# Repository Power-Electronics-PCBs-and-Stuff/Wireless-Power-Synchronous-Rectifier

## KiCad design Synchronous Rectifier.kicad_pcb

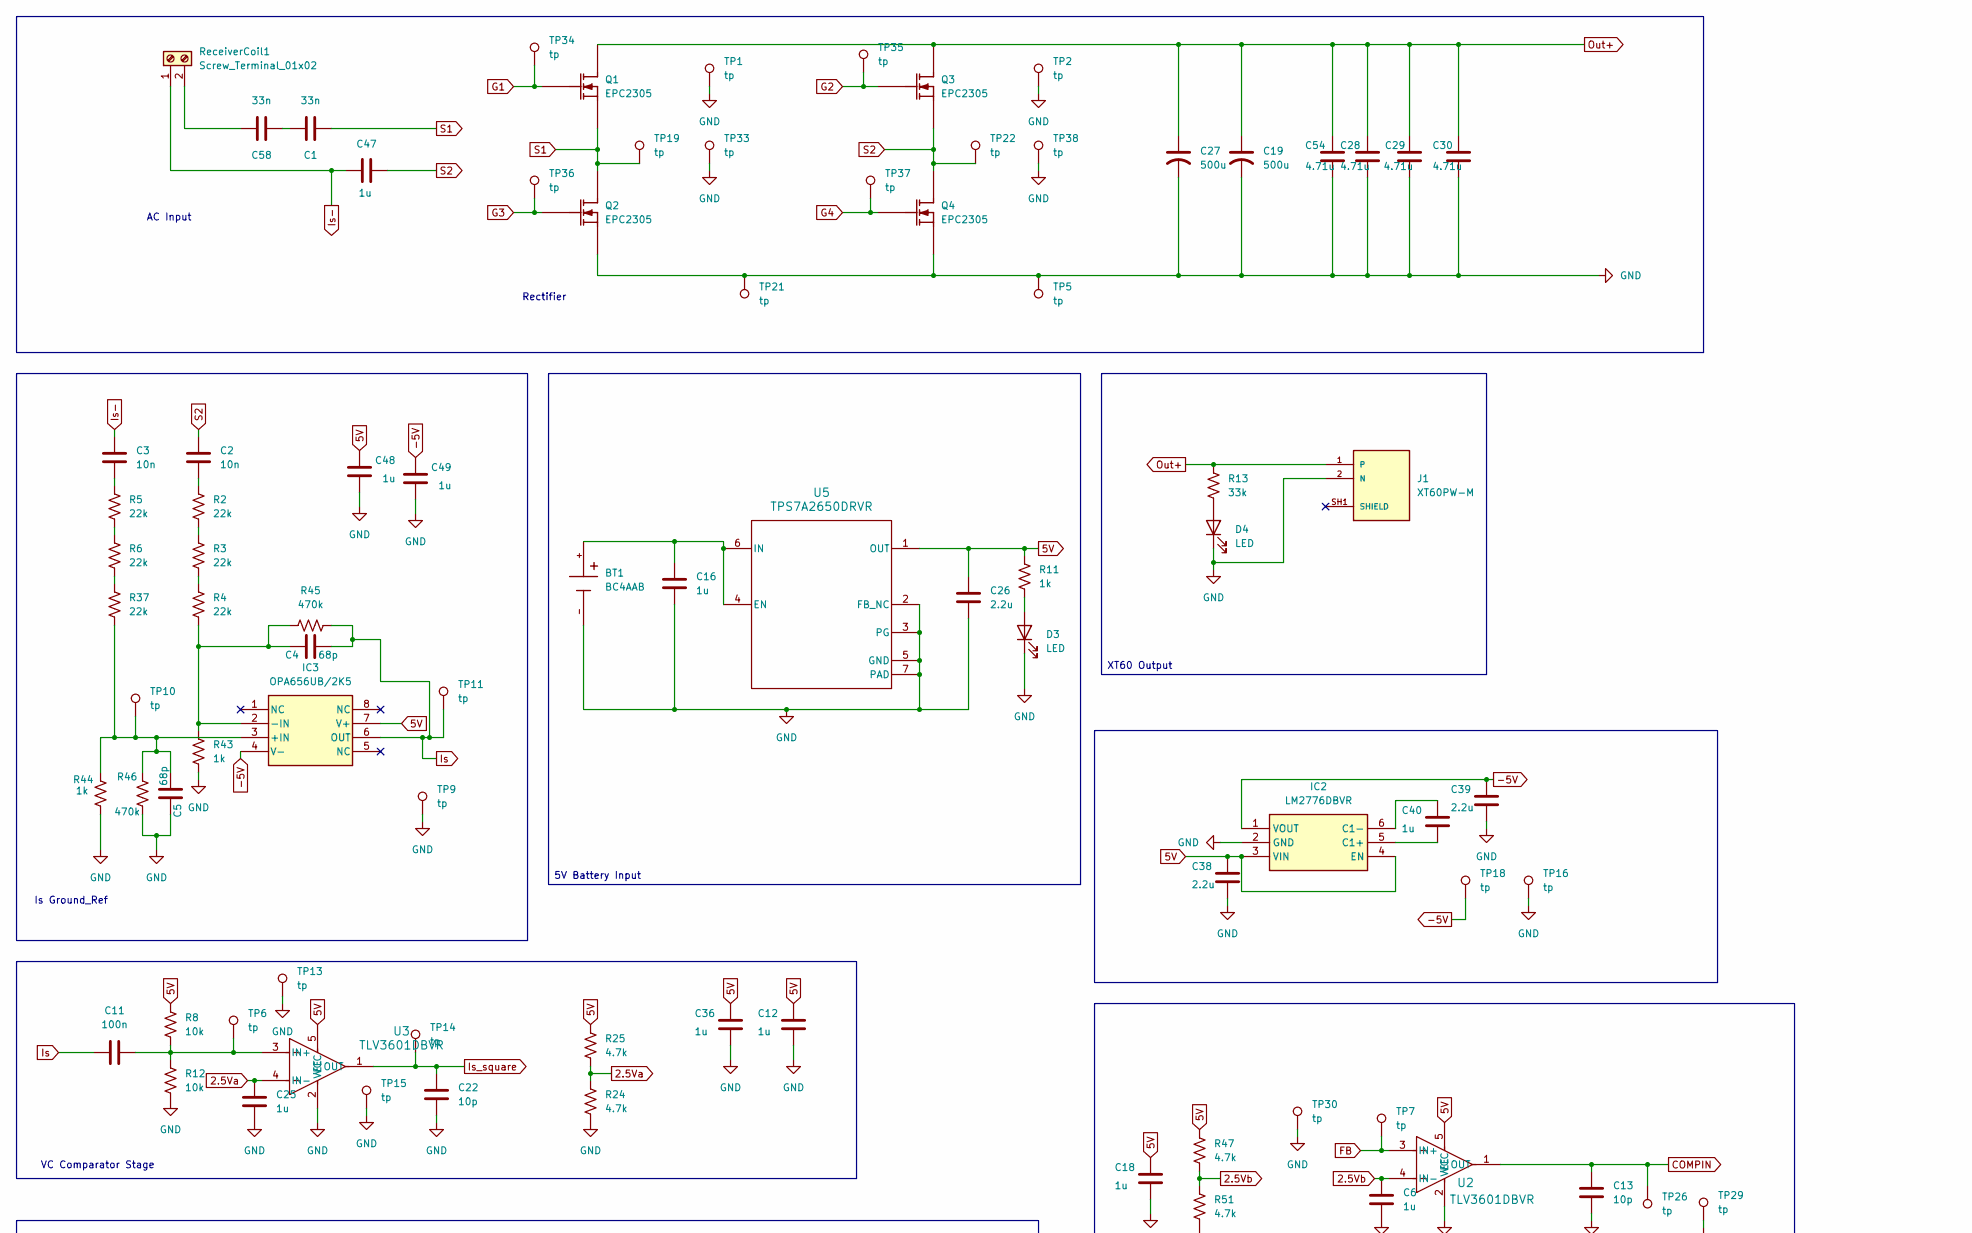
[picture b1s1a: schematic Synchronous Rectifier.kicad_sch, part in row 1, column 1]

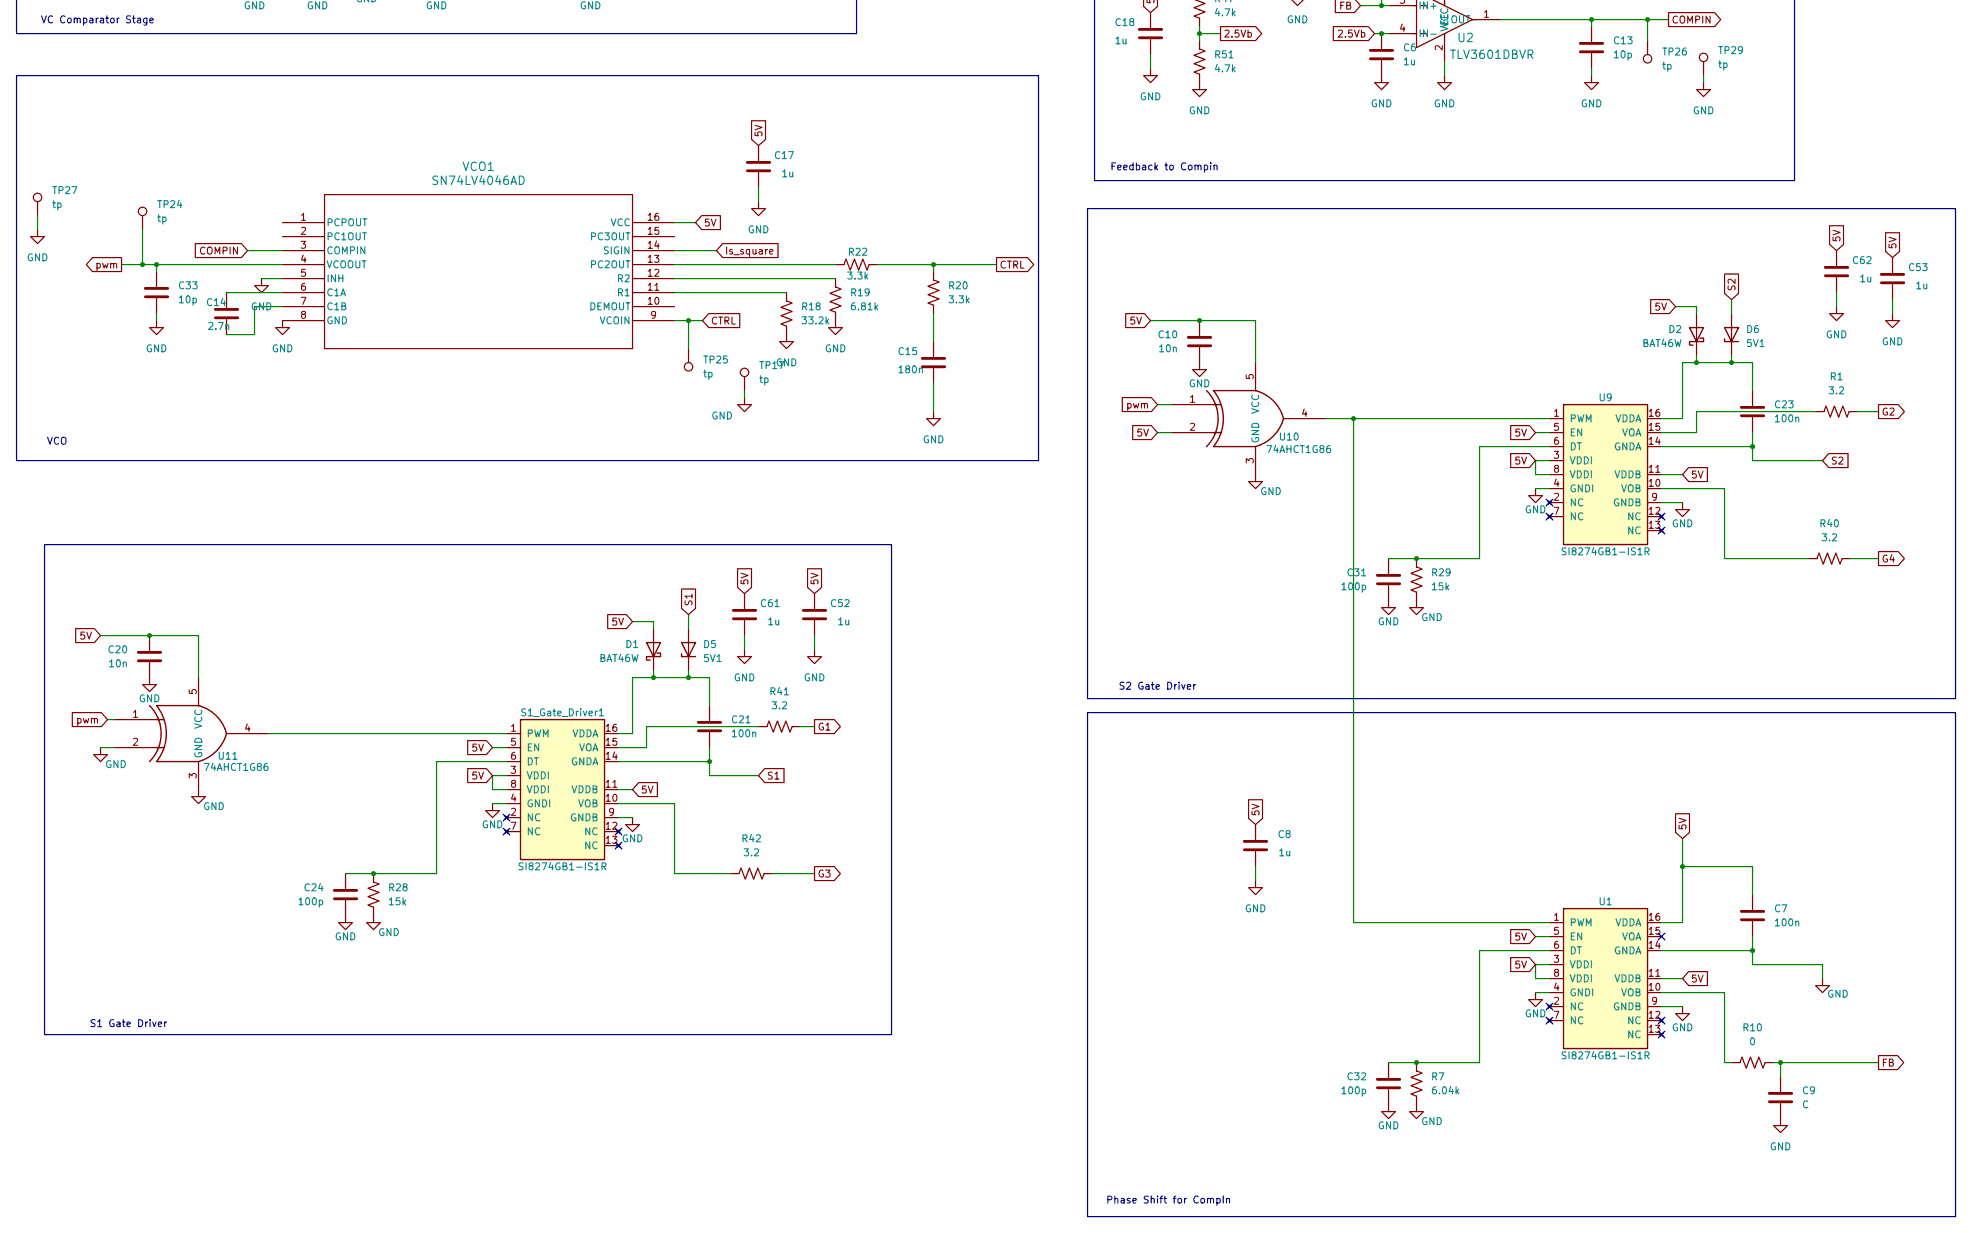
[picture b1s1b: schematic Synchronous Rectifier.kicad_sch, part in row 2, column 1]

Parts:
BT1: BC4AAB; BAT_BC4AAB; PARTREV E; DigiKey_Part_Number BC4AAB-ND
C1, C58: 33n; C_1206_3216Metric
C2, C3, C10, C20: 10n; C_0603_1608Metric
C4, C5: 68p; C_0603_1608Metric
C6, C8, C12, C16, C17, C18, C25, C36, C40, C48, C49, C52, C53, C61, C62: 1u; C_0603_1608Metric
C7, C11, C21, C23: 100n; C_0603_1608Metric
C9: C; C_0603_1608Metric
C13, C22, C33: 10p; C_0603_1608Metric
C14: 2.7n; C_0603_1608Metric
C15: 180n; C_0603_1608Metric
C19, C27: 500u; CP_Radial_D16.0mm_P7.50mm
C24, C31, C32: 100p; C_0603_1608Metric
C26, C38, C39: 2.2u; C_0603_1608Metric
C28, C29, C30, C54: 4.71u; C_1206_3216Metric
C47: 1u; C_1206_3216Metric
D1, D2: BAT46W; D_SOD-123F
D3, D4: LED; LED_0603_1608Metric
D5, D6: 5V1; D_SOD-123; MPN MMSZ5231B
IC2: LM2776DBVR; DBV0006A_N; Mouser Part Number 595-LM2776DBVR
IC3: OPA656UB/2K5; D8; Mouser Part Number 584-ADA4817-1ARDZ-R7
J1: XT60PW-M; AMASS_XT60PW-M; PARTREV 1.2
Q1, Q2, Q3, Q4: EPC2305; Manufacturer_Part_Number EPC2305
R1, R40, R41, R42: 3.2; R_0603_1608Metric
R2, R3, R4, R5, R6, R37: 22k; R_0603_1608Metric
R7: 6.04k; R_0603_1608Metric
R8, R12: 10k; R_0603_1608Metric
R10: 0; R_0603_1608Metric
R11, R43, R44: 1k; R_0603_1608Metric
R13: 33k; R_0603_1608Metric
R18: 33.2k; R_0603_1608Metric
R19: 6.81k; R_0603_1608Metric
R20, R22: 3.3k; R_0603_1608Metric
R24, R25, R47, R51: 4.7k; R_0603_1608Metric
R28, R29: 15k; R_0603_1608Metric
R45, R46: 470k; R_0603_1608Metric
ReceiverCoil1: Screw_Terminal_01x02; Molex_0389690002
S1_Gate_Driver1: SI8274GB1-IS1R; SOIC-16_3.9x9.9mm_P1.27mm; MPN SI8274GB1-IS1R
TP1, TP2, TP5, TP6, TP7, TP9, TP10, TP11, TP13, TP14, TP15, TP16, TP17, TP18, TP19, TP21, TP22, TP24, TP25, TP26, TP27, TP29, TP30, TP33, TP34, TP35, TP36, TP37, TP38: tp; TestPoint_THTPad_D2.0mm_Drill1.0mm
U1, U9: SI8274GB1-IS1R; SOIC-16_3.9x9.9mm_P1.27mm; MPN SI8274GB1-IS1R
U2: TLV3601DBVR; TSOT-23-5_HandSoldering
U3: TLV3601DBVR; SOT-23-5_HandSoldering
U5: TPS7A2650DRVR; DRV0006A_NV
U10, U11: 74AHCT1G86; DBV5
VCO1: SN74LV4046AD; D16

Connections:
2.5Va: C25.2, R24.1, R25.2, U3.4 (IN-)
2.5Vb: C6.2, R47.2, R51.1, U2.4 (IN-)
5V: C7.1, C8.2, C10.1, C12.2, C17.2, C18.2, C20.1, C26.1, C36.2, C38.2, C48.2, C52.2, C53.2, C61.2, C62.2, D1.2 (A), D2.2 (A), IC2.3 (VIN), IC2.4 (EN), IC3.7 (V+), R8.1, R11.1, R25.1, R47.1, S1_Gate_Driver1.3 (VDDI), S1_Gate_Driver1.5 (EN), S1_Gate_Driver1.8 (VDDI), S1_Gate_Driver1.11 (VDDB), U1.3 (VDDI), U1.5 (EN), U1.8 (VDDI), U1.11 (VDDB), U1.16 (VDDA), U2.5 (VCC), U3.5 (VCC), U5.1 (OUT), U9.3 (VDDI), U9.5 (EN), U9.8 (VDDI), U9.11 (VDDB), U10.2, U10.5 (VCC), U11.5 (VCC), VCO1.16 (VCC)
-5V: C39.2, C49.2, IC2.1 (VOUT), IC3.4 (V-), TP18.1 (1_1)
COMPIN: C13.1, TP26.1 (1_1), U2.1 (OUT), VCO1.3 (COMPIN)
CTRL: R20.1, R22.1, TP25.1 (1_1), VCO1.9 (VCOIN)
FB: C9.1, R10.2, TP7.1 (1_1), U2.3 (IN+)
G1: Q1.1 (G_1), Q1.12 (G_2), R41.2, TP34.1 (1_1)
G2: Q3.1 (G_1), Q3.12 (G_2), R1.2, TP35.1 (1_1)
G3: Q2.1 (G_1), Q2.12 (G_2), R42.2, TP36.1 (1_1)
G4: Q4.1 (G_1), Q4.12 (G_2), R40.2, TP37.1 (1_1)
GND: BT1.-, C5.2, C6.1, C7.2, C8.1, C9.2, C10.2, C12.1, C13.2, C15.1, C16.2, C17.1, C18.1, C19.2, C20.2, C22.2, C24.2, C25.1, C26.2, C27.2, C28.1, C29.1, C30.1, C31.2, C32.2, C33.2, C36.1, C38.1, C39.1, C48.1, C49.1, C52.1, C53.1, C54.1, C61.1, C62.1, D3.1 (K), D4.1 (K), IC2.2 (GND), J1.2 (N), Q2.2 (S_1), Q2.4 (S_2), Q2.6 (S_3), Q2.13 (S_4), Q2.14 (S_5), Q2.15 (S_6), Q4.2 (S_1), Q4.4 (S_2), Q4.6 (S_3), Q4.13 (S_4), Q4.14 (S_5), Q4.15 (S_6), R7.2, R12.1, R18.1, R19.1, R24.2, R28.2, R29.2, R43.2, R44.2, R46.1, R51.2, S1_Gate_Driver1.4 (GNDI), S1_Gate_Driver1.9 (GNDB), TP1.1 (1_1), TP2.1 (1_1), TP5.1 (1_1), TP9.1 (1_1), TP13.1 (1_1), TP15.1 (1_1), TP16.1 (1_1), TP17.1 (1_1), TP21.1 (1_1), TP27.1 (1_1), TP29.1 (1_1), TP30.1 (1_1), TP33.1 (1_1), TP38.1 (1_1), U1.4 (GNDI), U1.9 (GNDB), U1.14 (GNDA), U2.2 (VEE), U3.2 (VEE), U5.2 (FB_NC), U5.3 (PG), U5.5 (GND), U5.7 (PAD), U9.4 (GNDI), U9.9 (GNDB), U10.3 (GND), U11.2, U11.3 (GND), VCO1.5 (INH), VCO1.8 (GND)
Is: C4.1, C11.1, IC3.6 (OUT), R45.2, TP11.1 (1_1)
Is-: C3.1, C47.2, ReceiverCoil1.1
Is_square: C22.1, TP14.1 (1_1), U3.1 (OUT), VCO1.14 (SIGIN)
unnamed: C1.1, C58.2
unnamed: C2.2, R2.1
unnamed: C3.2, R5.1
unnamed: C15.2, R20.2
unnamed: C21.1, D1.1 (K), D5.1 (K), S1_Gate_Driver1.16 (VDDA)
unnamed: C23.1, D2.1 (K), D6.1 (K), U9.16 (VDDA)
unnamed: D3.2 (A), R11.2
unnamed: D4.2 (A), R13.2
unnamed: C40.1, IC2.5 (C1+)
unnamed: C40.2, IC2.6 (C1-)
unnamed: C5.1, IC3.3 (+IN), R37.2, R44.1, R46.2, TP10.1 (1_1)
unnamed: C4.2, IC3.2 (-IN), R4.2, R43.1, R45.1
unnamed: R2.2, R3.1
unnamed: R3.2, R4.1
unnamed: R5.2, R6.1
unnamed: R6.2, R37.1
unnamed: C58.1, ReceiverCoil1.2
unnamed: C24.1, R28.1, S1_Gate_Driver1.6 (DT)
unnamed: S1_Gate_Driver1.1 (PWM), U11.4
unnamed: R41.1, S1_Gate_Driver1.15 (VOA)
unnamed: R42.1, S1_Gate_Driver1.10 (VOB)
unnamed: C32.1, R7.1, U1.6 (DT)
unnamed: U1.1 (PWM), U9.1 (PWM), U10.4
unnamed: R10.1, U1.10 (VOB)
unnamed: C11.2, R8.2, R12.2, TP6.1 (1_1), U3.3 (IN+)
unnamed: BT1.+, C16.1, U5.4 (EN), U5.6 (IN)
unnamed: C31.1, R29.1, U9.6 (DT)
unnamed: R1.1, U9.15 (VOA)
unnamed: R40.1, U9.10 (VOB)
unnamed: C14.2, VCO1.6 (C1A)
unnamed: C14.1, VCO1.7 (C1B)
unnamed: R22.2, VCO1.13 (PC2OUT)
unnamed: R18.2, VCO1.11 (R1)
unnamed: R19.2, VCO1.12 (R2)
Out+: C19.1, C27.1, C28.2, C29.2, C30.2, C54.2, J1.1, Q1.3 (D_1), Q1.5 (D_2), Q1.7 (D_3), Q1.8 (D_4), Q1.9 (D_5), Q1.10 (D_6), Q1.11 (D_7), Q3.3 (D_1), Q3.5 (D_2), Q3.7 (D_3), Q3.8 (D_4), Q3.9 (D_5), Q3.10 (D_6), Q3.11 (D_7), R13.1
S1: C1.2, C21.2, D5.2 (A), Q1.2 (S_1), Q1.4 (S_2), Q1.6 (S_3), Q1.13 (S_4), Q1.14 (S_5), Q1.15 (S_6), Q2.3 (D_1), Q2.5 (D_2), Q2.7 (D_3), Q2.8 (D_4), Q2.9 (D_5), Q2.10 (D_6), Q2.11 (D_7), S1_Gate_Driver1.14 (GNDA), TP19.1 (1_1)
S2: C2.1, C23.2, C47.1, D6.2 (A), Q3.2 (S_1), Q3.4 (S_2), Q3.6 (S_3), Q3.13 (S_4), Q3.14 (S_5), Q3.15 (S_6), Q4.3 (D_1), Q4.5 (D_2), Q4.7 (D_3), Q4.8 (D_4), Q4.9 (D_5), Q4.10 (D_6), Q4.11 (D_7), TP22.1 (1_1), U9.14 (GNDA)
pwm: C33.1, TP24.1 (1_1), U10.1, U11.1, VCO1.4 (VCOOUT)

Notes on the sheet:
VCO
S2 Gate Driver
Feedback to Compin
VC Comparator Stage
S1 Gate Driver
Rectifier
Is Ground_Ref
AC Input
Phase Shift for CompIn
XT60 Output
5V Battery Input

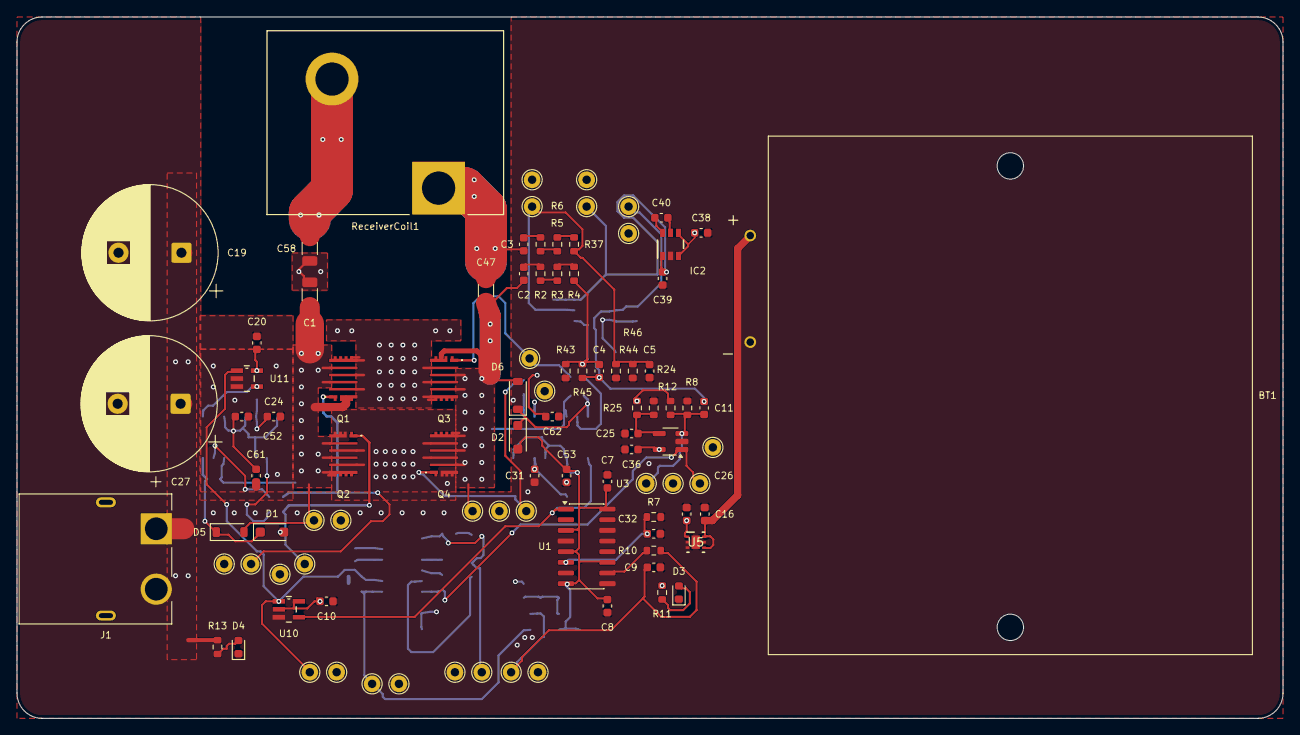
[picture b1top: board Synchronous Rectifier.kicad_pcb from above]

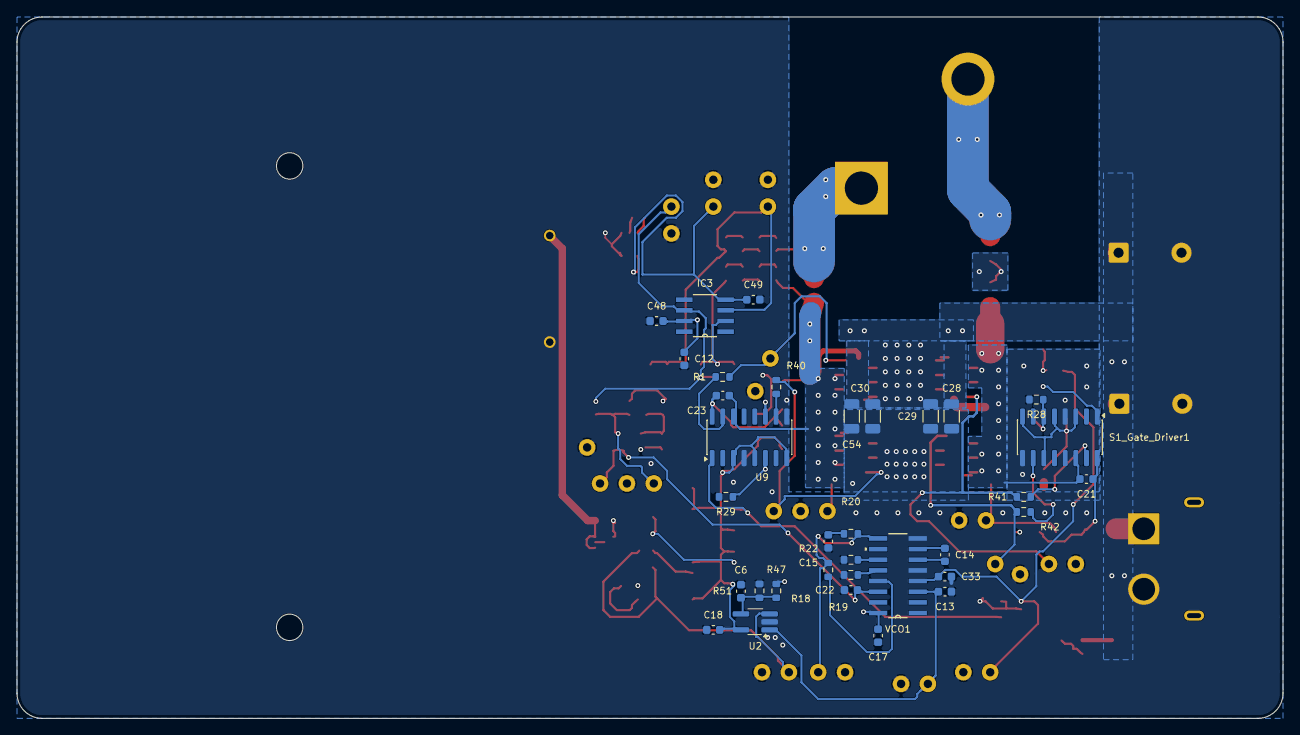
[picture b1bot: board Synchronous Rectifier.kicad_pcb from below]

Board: 4 copper layers, 150.9 x 83.6 mm, 129 parts (34 on the bottom side), 53 nets.

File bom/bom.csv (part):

Reference,Qty,Value,Footprint,MPN,Manufacturer,DigiKey,DK_Stock,Mouser,MO_Stock,Chosen_Distributor,Datasheet,Validated,DNP,Notes
BT1,1,BC4AAB,BAT_BC4AAB,BC4AAB,MPD,BC4AAB-ND,16,,,DigiKey,,yes (digikey.com page 2026-11-09),,"DigiKey shows 16 on hand + 13,400 factory stock"
"C1,C58",2,33n,1206,,,,,,,,,no,,UNSOURCED: 33 nF in series with the coil sees ~11 A RMS and ~210 V RMS at 250 kHz; no single 1206 part exists. Needs a parallel C0G bank (e.g. 10x KEMET C1206C332JCGACAUTO 3.3 nF 500 V C0G) or a film capacitor; schematic/PCB change required
"C3,C10,C20,C2",4,10n,0603,CL10B103KB8NNNC,Samsung Electro-Mechanics,1276-1009-1-ND,5504,,,DigiKey,,yes (digikey.com page 2026-11-09),,10 nF 50 V X7R 0603
"C4,C5",2,68p,0603,CL10C680JB8NNNC,Samsung Electro-Mechanics,1276-1135-1-ND,207000,,,DigiKey,,yes (digikey.com page 2026-11-09),,68 pF 50 V C0G 0603
C9,1,C,0603,,,,,,,,,no,,"UNSOURCED: schematic value is ""C"" (no capacitance given) - set the value first"
"C11,C23,C7,C21",4,100n,0603,C0603C104K5RACTU,KEMET,399-C0603C104K5RACTUCT-ND,2485421,,,DigiKey,,yes (digikey.com page 2026-11-09),,100 nF 50 V X7R 0603 (Samsung CL10B104KB8NNNC is on 61-week backorder)
"C13,C33,C22",3,10p,0603,CL10C100JB8NNNC,Samsung Electro-Mechanics,1276-1027-1-ND,206747,,,DigiKey,,yes (digikey.com page 2026-11-09),,10 pF 50 V C0G 0603
C14,1,2.7n,0603,GRM1885C1H272JA01D,Murata Electronics,490-3283-1-ND,293979,,,DigiKey,,yes (digikey.com page 2026-11-09),,2.7 nF 50 V C0G 0603
C15,1,180n,0603,CC0603KRX7R8BB184,YAGEO,13-CC0603KRX7R8BB184CT-ND,19322,,,DigiKey,,yes (digikey.com page 2026-11-09),,180 nF 25 V X7R 0603 (no 50 V 0.18 uF 0603 stocked; node is 5 V)
"C19,C27",2,500u,CP_Radial_D16.0mm_P7.50mm,UPW2A471MHD,Nichicon,493-1985-ND,5222,,,DigiKey,,yes (digikey.com page 2026-11-09),,"470 uF 100 V substituted for 500 uF; 16 mm dia, 7.5 mm pitch, 31.5 mm tall; ripple 1.31 A @100 kHz; status Not-For-New-Designs (Panasonic EEU-FC2A471 is obsolete)"
"C32,C24,C31",3,100p,0603,CL10C101JB8NNNC,Samsung Electro-Mechanics,1276-1008-1-ND,1155305,,,DigiKey,,yes (digikey.com page 2026-11-09),,100 pF 50 V C0G 0603
"C38,C26,C39",3,2.2u,0603,GRM188Z71E225KE43D,Murata Electronics,490-GRM188Z71E225KE43DCT-ND,147724,,,DigiKey,,yes (digikey.com page 2026-11-09),,"2.2 uF 25 V 0603 (DigiKey lists X7R; Murata ""Z7"" code is X7T class)"
"C40,C16,C36,C6,C17,C8,C49,C52,C18,C53,C62,C61,C25,C48,C12",15,1u,0603,UMK107AB7105KA-T,Taiyo Yuden,587-3247-1-ND,579237,,,DigiKey,,yes (digikey.com page 2026-11-09),,1 uF 50 V X7R 0603
C47,1,1u,1206,C1206C105K1RACTU,KEMET,399-C1206C105K1RACTUCT-ND,31698,,,DigiKey,,yes (digikey.com page 2026-11-09),,1 uF 100 V X7R 1206 (Murata GRM31CR72A105KA01L backordered to Feb 2027). Also in the 11 A tank path - same cap-bank concern as C1/C58
"C54,C28,C30,C29",4,4.71u,1206,GRJ31CZ72A475KE01L,Murata Electronics,490-GRJ31CZ72A475KE01LCT-ND,66536,,,DigiKey,,yes (digikey.com page 2026-11-09),,4.7 uF 100 V X7R 1206 soft-termination (GRM31CR72A475KE11L not stocked)
"D2,D1",2,BAT46W,SOD-123F,BAT46W,Diotec Semiconductor,4878-BAT46WCT-ND,83359,,,DigiKey,https://datasheet.lcsc.com/lcsc/2204281430_Guangdong-Hottech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,yes (digikey.com page 2026-11-09),,SOD-123 part on the SOD-123F footprint (pad pitch compatible). Vishay BAT46W-E3-08 backordered to Jan 2027
"D3,D4",2,LED,0603,LTST-C190GKT,Lite-On Inc.,160-LTST-C190GKTCT-ND,1187734,,,DigiKey,,yes (digikey.com page 2026-11-09),,green 0603 LED
"D6,D5",2,5V1,SOD-123,MMSZ5231BT1G,onsemi,MMSZ5231BT1GOSCT-ND,76458,,,DigiKey,https://www.onsemi.com/pdf/datasheet/mmsz5221bt1-d.pdf,yes (digikey.com page 2026-11-09),,5.1 V 500 mW Zener SOD-123
IC2,1,LM2776DBVR,DBV0006A_N,LM2776DBVR,Texas Instruments,296-43957-1-ND,46809,595-LM2776DBVR,,DigiKey,http://www.ti.com/lit/gpn/lm2776,yes (digikey.com page 2026-11-09),,
IC3,1,OPA656UB/2K5,D8,OPA656UB/2K5,Texas Instruments,296-OPA656UB/2K5CT-ND,3184,584-ADA4817-1ARDZ-R7,,DigiKey,https://www.ti.com/lit/gpn/opa656,yes (digikey.com page 2026-11-09),,schematic MPN field said ADA4817-1ARDZ-R7 (left over from the sample board) - corrected to the OPA656 the symbol and footprint describe
J1,1,XT60PW-M,AMASS_XT60PW-M,XT60PW-M,AMASS,,,,,Amazon,,no,,"AMAZON: right-angle PCB-mount XT60 male; candidate listings B0DTGCK8VF (Gaslos, 90-degree XT60PW male/female) and B07VRLQ2C5 (Yiqigou, XT60PW pairs). Amazon blocks automated browsing - confirm the listing shows the XT60PW-M (male, PCB, 90 degree) before ordering"
"Q4,Q1,Q2,Q3",4,EPC2305,EPC2305,EPC2305,EPC,917-EPC2305CT-ND,15878,,,DigiKey,https://epc-co.com/epc/products/gan-fets-and-ics/epc2305,yes (digikey.com page 2026-11-09),,150 V GaN FET
"R1,R40,R41,R42",4,3.2,0603,ERJ-3RQF3R3V,Panasonic Industry,P3.3AJCT-ND,5604,,,DigiKey,,yes (digikey.com page 2026-11-09),,3.3 ohm substituted for 3.2 ohm (3.2 is not an E24/E96 value stocked in 0603)
R7,1,6.04k,0603,ERJ-3EKF6041V,Panasonic Industry,P6.04KHCT-ND,36474,,,DigiKey,,yes (digikey.com page 2026-11-09),,
"R8,R12",2,10k,0603,ERJ-3EKF1002V,Panasonic Industry,P10.0KHCT-ND,621467,,,DigiKey,,yes (digikey.com page 2026-11-09),,
R10,1,0,0603,ERJ-3GEY0R00V,Panasonic Industry,P0.0GCT-ND,4415369,,,DigiKey,,yes (digikey.com page 2026-11-09),,0 ohm jumper
"R11,R43,R44",3,1k,0603,ERJ-3EKF1001V,Panasonic Industry,P1.00KHCT-ND,4055833,,,DigiKey,,yes (digikey.com page 2026-11-09),,
R13,1,33k,0603,ERJ-3EKF3302V,Panasonic Industry,P33.0KHCT-ND,93742,,,DigiKey,,yes (digikey.com page 2026-11-09),,
R18,1,33.2k,0603,ERJ-3EKF3322V,Panasonic Industry,P33.2KHCT-ND,89962,,,DigiKey,,yes (digikey.com page 2026-11-09),,
R19,1,6.81k,0603,ERJ-3EKF6811V,Panasonic Industry,P6.81KHCT-ND,1074,,,DigiKey,,yes (digikey.com page 2026-11-09),,DigiKey page is tagged Marketplace - may ship separately
"R20,R22",2,3.3k,0603,ERJ-3EKF3301V,Panasonic Industry,P3.30KHCT-ND,359068,,,DigiKey,,yes (digikey.com page 2026-11-09),,
"R24,R51,R25,R47",4,4.7k,0603,ERJ-3EKF4701V,Panasonic Industry,P4.70KHCT-ND,783994,,,DigiKey,,yes (digikey.com page 2026-11-09),,
"R29,R28",2,15k,0603,ERJ-3EKF1502V,Panasonic Industry,P15.0KHCT-ND,48445,,,DigiKey,,yes (digikey.com page 2026-11-09),,
"R37,R4,R2,R6,R5,R3",6,22k,0603,ERJ-3EKF2202V,Panasonic Industry,P22.0KHCT-ND,184599,,,DigiKey,,yes (digikey.com page 2026-11-09),,
"R45,R46",2,470k,0603,ERJ-3EKF4703V,Panasonic Industry,P470KHCT-ND,50008,,,DigiKey,,yes (digikey.com page 2026-11-09),,
ReceiverCoil1,1,Screw_Terminal_01x02,Molex_0389690002,0389690002,Molex,WM7469-ND,4511,,,DigiKey,,yes (digikey.com page 2026-11-09),,"2-circuit barrier terminal block, 12.7 mm pitch, PC-pin"
"S1_Gate_Driver1,U9,U1",3,SI8274GB1-IS1R,SOIC-16_3.9x9.9mm_P1.27mm,SI8274GB1-IS1R,Skyworks Solutions Inc.,336-5554-1-ND,1683,,,DigiKey,https://www.skyworksinc.com/Products/Isolation/Si827x-Isolat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,yes (digikey.com page 2026-11-09),,
"TP27,TP16,TP22,TP25,TP33,TP24,TP15,TP11,TP36,TP10,TP14,TP29,TP1,TP26,TP7,TP21,TP13,TP19,TP5,TP17,TP35,TP2,TP6,TP37,TP18,TP9,TP38,TP30,TP34",29,tp,TestPoint_THTPad_D2.0mm_Drill1.0mm,,,,,,,,,n/a,,bare 2 mm PTH test pad - nothing to order
U2,1,TLV3601DBVR,TSOT-23-5_HandSoldering,TLV3601DBVR,Texas Instruments,296-TLV3601DBVRCT-ND,5188,,,DigiKey,https://www.ti.com/lit/gpn/tlv3601,yes (digikey.com page 2026-11-09),,SOT-23-5 part; U2 footprint is TSOT-23-5 (same land pattern)
U3,1,TLV3601DBVR,SOT-23-5_HandSoldering,TLV3601DBVR,Texas Instruments,296-TLV3601DBVRCT-ND,5188,,,DigiKey,https://www.ti.com/lit/gpn/tlv3601,yes (digikey.com page 2026-11-09),,
U4,1,TPS7A2550DRVR,DRV0006A-IPC_A,TPS7A2650DRVR,Texas Instruments,296-TPS7A2650DRVRCT-ND,5219,,,DigiKey,https://www.ti.com/lit/gpn/tps7a25,yes (digikey.com page 2026-11-09),,"SUBSTITUTE for TPS7A2550DRVR (DigiKey backordered to May 2027). TPS7A26 fixed-5V WSON-6 is pin-identical (OUT/NC/PG/EN/GND/IN, checked in both datasheets), 500 mA, Vin 2.4-18 V, needs >=1 uF out (C26 = 2.2 uF)"
"U11,U10",2,74AHCT1G86,DBV5,SN74AHCT1G86DBVR,Texas Instruments,296-4714-1-ND,770,,,DigiKey,http://www.ti.com/lit/sg/scyt129e/scyt129e.pdf,yes (digikey.com page 2026-11-09),,
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
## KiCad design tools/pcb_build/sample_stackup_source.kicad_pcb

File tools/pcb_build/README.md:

# PCB layout generator (scripted, KiCad 10)

The board in `../../Synchronous Rectifier.kicad_pcb` was produced by these scripts, run with KiCad's bundled
Python (`C:\Program Files\KiCad\10.0\bin\python.exe`). Re-running regenerates the whole layout from an
un-routed board that has the footprints and nets from the schematic.

Workflow when the schematic changes:
1. In KiCad: Tools -> Update PCB from Schematic (keeps nets/footprints in sync). Close the PCB editor.
2. Copy the PCB as the build input (the scripts call it `base2.kicad_pcb`):
   `cp "../../Synchronous Rectifier.kicad_pcb" base2.kicad_pcb`
   (new reference designators need an entry in the `PL` placement table in `build_pcb.py`).
3. `./multi.sh` tries several routing orders and keeps the first fully-routed result (`v*.kicad_pcb`).
4. `python finish.py <board> sample_stackup_source.kicad_pcb <project.kicad_pro>` writes the 4-layer
   stackup (2 oz outer) into the board and the net classes/rules into the project file.
5. `"C:\Program Files\KiCad\10.0\bin\python.exe" check_board.py <board> --drc` for a summary + kicad-cli DRC.
6. Copy the board over the project PCB (back it up first), then run the kicad-happy analyzers
   (`analyze_pcb.py --full --schematic ...`, `cross_analysis.py`, `analyze_emc.py`) with `--analysis-dir analysis/`.

Files: `build_pcb.py` (placement table, zones, via arrays, power copper, GND-pocket stitching, reference text),
`router.py` (grid A* router on F/B with vias; 5V drops into the In1 plane), `finish.py`, `check_board.py`,
`islands.py` (lists zone fill islands), `drcsum.py` (groups a kicad-cli DRC report), `render.sh`/`crop.sh`
(PDF -> PNG previews via pdftoppm).

## v30 additions (2026-11-08)
- `run_v30.sh` = multi-seed routed build + finish + DRC; `post_v30.sh` installs the board when DRC is clean and runs the
  kicad-happy analyzers; `multi.sh` picks the best fully routed seed by `score.py`.
- `current_check.py <board>`: copper width per layer across named cut lines -> IPC-2221 ampacity table (edit `CUTS`).
- `pair_check.py <board>`: lengths of the signal pairs, remaining right-angle corners, decoupling-cap axis vs. pin.
- In `build_pcb.py`: `place_near`/`place_between` (decoupling and bootstrap caps), `pair_testpoints` (GND test point next
  to every signal test point, `FIXED_GND` for hand-placed ones), `chamfer_tracks` (45-degree mitres after routing),
  hand-routed G1/G3 gate tracks, bridge caps C28/C29/C30/C54 under the FET columns on the `OUTB` Out+ pour.

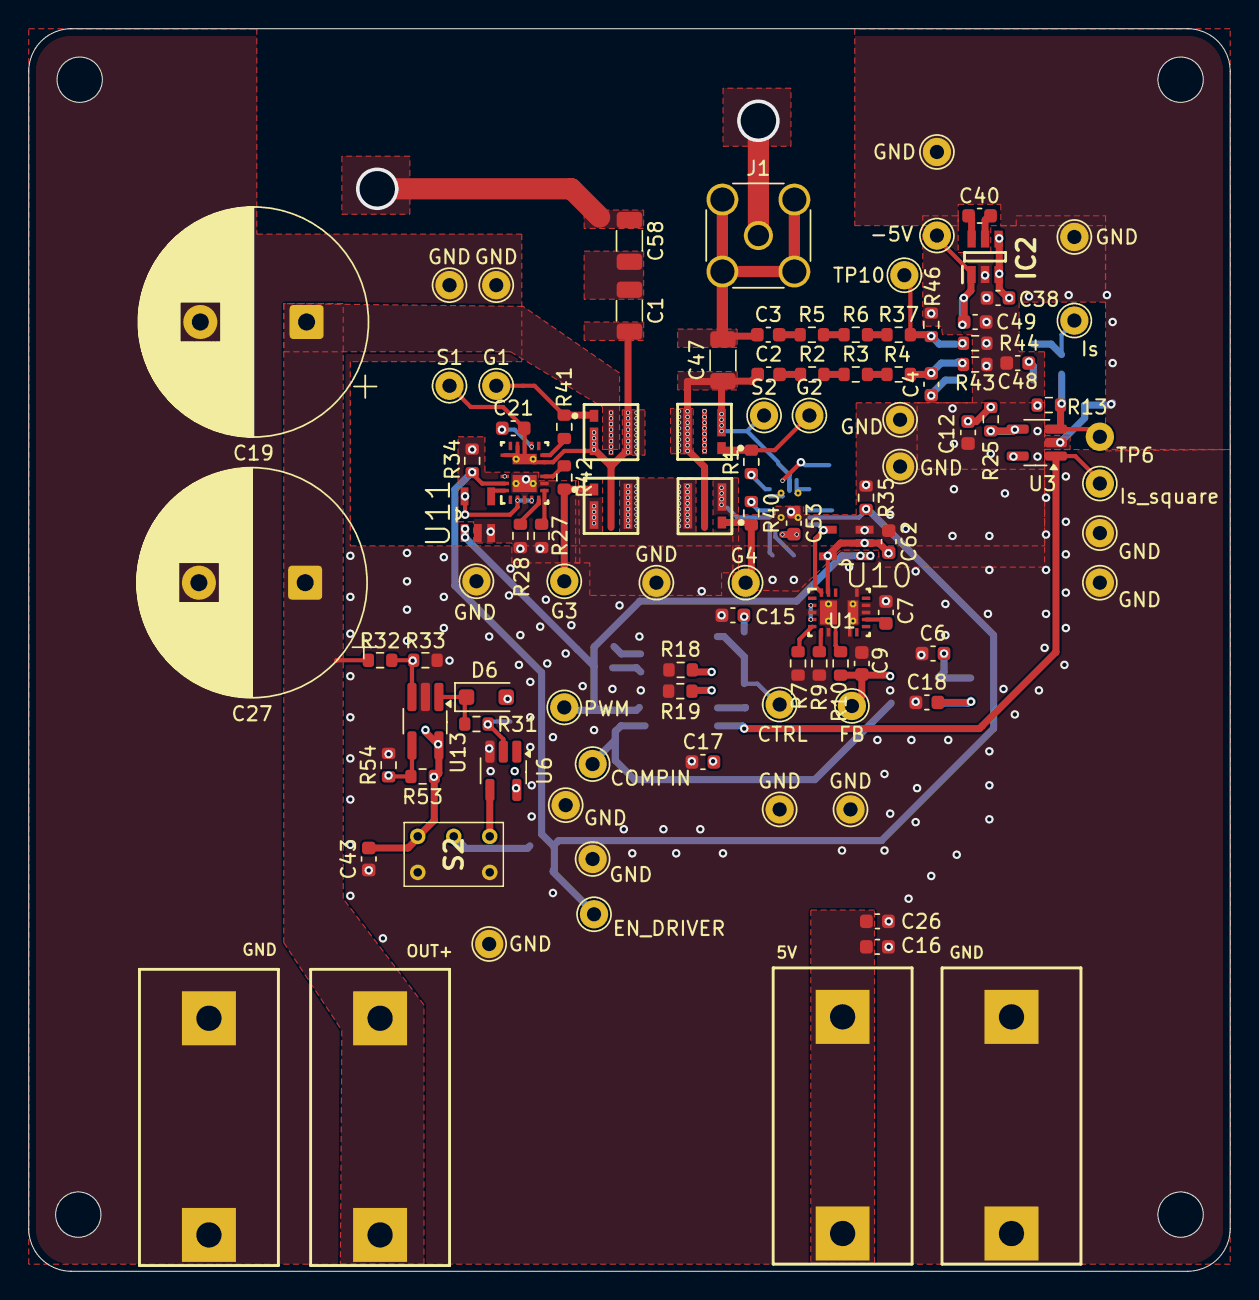
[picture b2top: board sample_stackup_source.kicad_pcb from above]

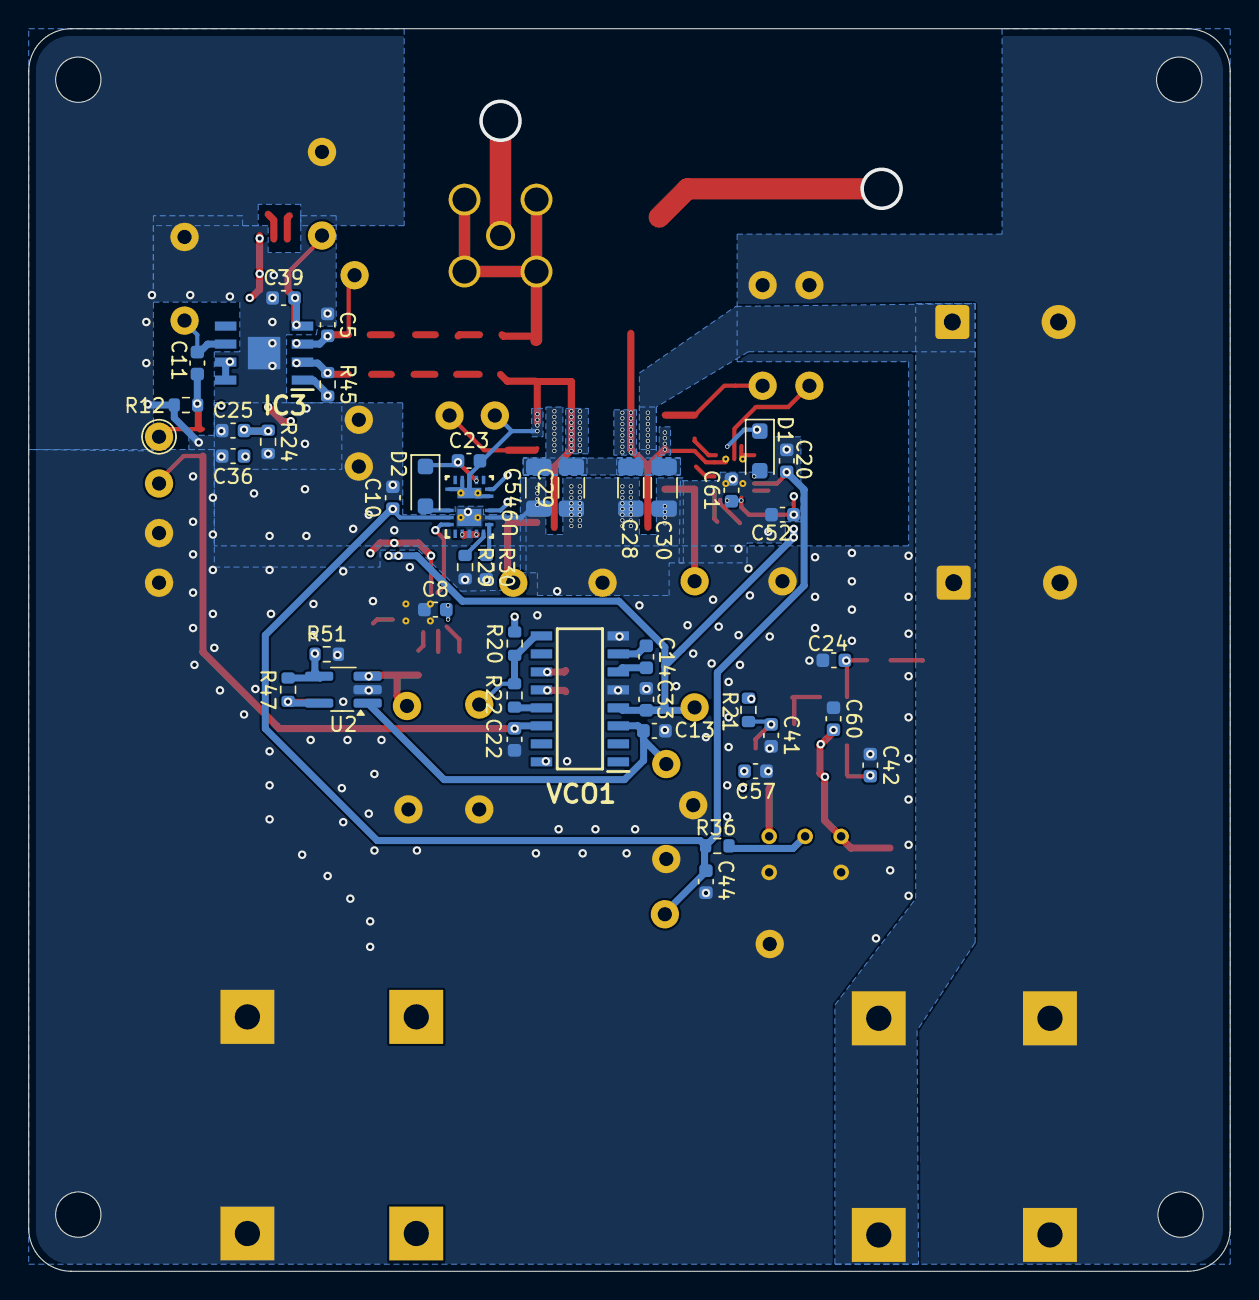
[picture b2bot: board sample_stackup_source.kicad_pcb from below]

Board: 4 copper layers, 84.8 x 87.7 mm, 146 parts (43 on the bottom side), 64 nets.

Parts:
5V: Conn_Plug_2P; 571-0500
-5V: tp; TestPoint_THTPad_D2.0mm_Drill1.0mm
C1, C58: 1.1n; C_1206_3216Metric
C2, C3, C10, C11, C15, C20, C44: 10n; C_0603_1608Metric
C4, C5: 68p; C_0603_1608Metric
C6, C8, C12, C16, C17, C18, C25, C36, C40, C42, C43, C48, C49, C52, C53, C57, C60, C61, C62: 1u; C_0603_1608Metric
C7, C21, C23, C41: 100n; C_0603_1608Metric
C9: 300p; C_0603_1608Metric
C13, C22, C33: 10p; C_0603_1608Metric
C14: 51p; C_0603_1608Metric
C19, C27: 500u; CP_Radial_D16.0mm_P7.50mm
C24: 47p; C_0603_1608Metric
C26: 10u; C_0603_1608Metric
C28, C29, C30, C54: 10u; C_1206_3216Metric
C38, C39: 2.2u; C_0603_1608Metric
C47: 2.2n; C_1206_3216Metric
COMPIN: tp; TestPoint_THTPad_D2.0mm_Drill1.0mm
CTRL: tp; TestPoint_THTPad_D2.0mm_Drill1.0mm
D1, D2, D6: BAT46W; D_SOD-123F
EN_DRIVER: tp; TestPoint_THTPad_D2.0mm_Drill1.0mm
FB: tp; TestPoint_THTPad_D2.0mm_Drill1.0mm
G1, G2, G3, G4: tp; TestPoint_THTPad_D2.0mm_Drill1.0mm
GND: tp; TestPoint_THTPad_D2.0mm_Drill1.0mm
GND#2, GND#3, GND#4, GND#5, GND#6, GND#8, GND#9, GND#10, GND#11, GND#12, GND#14, GND#15, GND#16, GND#17: tp; TestPoint_THTPad_D2.0mm_Drill1.0mm
GND#7, GND#13: Conn_Plug_2P; 571-0500
IC2: LM2776DBVR; SOT95P280X145-6N
IC3: ADA4817-1ARDZ-R7; SOIC127P600X175-9N
Is: tp; TestPoint_THTPad_D2.0mm_Drill1.0mm
Is_square: tp; TestPoint_THTPad_D2.0mm_Drill1.0mm
J1: Conn_Coaxial; SMA_Amphenol_132134_Vertical
OUT+: Conn_Plug_2P; 571-0500
PWM: tp; TestPoint_THTPad_D2.0mm_Drill1.0mm
Q1, Q2, Q3, Q4: IGB110S10S1; IFX-PG-TSON-4-2-V
R1, R10, R40, R41, R42: 10; R_0603_1608Metric
R2, R3, R4, R5, R6, R24, R25, R37, R47, R51, R53, R54: 4.7k; R_0603_1608Metric
R7, R9: 1.78Meg; R_0603_1608Metric
R12, R13, R20, R22, R43, R44: 1k; R_0603_1608Metric
R18: 32.4k; R_0603_1608Metric
R19: 18.7K; R_0603_1608Metric
R21: 100; R_0603_1608Metric
R27, R28, R29, R30: 60.4K; R_0603_1608Metric
R31: 100k; R_0603_1608Metric
R32: 681k; R_0603_1608Metric
R33, R34, R35: 47k; R_0603_1608Metric
R36: 470; R_0603_1608Metric
R45, R46: 14.7k; R_0603_1608Metric
S1, S2: tp; TestPoint_THTPad_D2.0mm_Drill1.0mm
S1_Gate_Driver1: LMG1210RVRR; RVR0019A
S2#2: G13AP
TP6, TP10: tp; TestPoint_THTPad_D2.0mm_Drill1.0mm
U1, U9: LMG1210RVRR; RVR0019A
U2, U13: TLV3601DBVR; TSOT-23-5_HandSoldering
U3: TLV3601DBVR; SOT-23-5_HandSoldering
U6: 74LVC1G17; SOT-23-5_HandSoldering
U10, U11: 74AHCT1G86; SOT95P280X145-5N
VCO1: SN74LV4046AD; SOIC127P600X175-16N

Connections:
2.5Va: C25.2, R24.1, R25.2, U3.4 (IN-)
2.5Vb: C6.2, R47.2, R51.1, U2.4 (IN-)
2.5Vc: C42.2, R53.2, R54.1, U13.4 (IN-)
5V: 5V.1 (L), 5V.2 (N), C8.2, C12.2, C16.2, C17.2, C18.2, C26.2, C36.2, C38.2, C43.2, C48.2, C52.2, C53.2, C57.2, C60.2, C61.2, C62.2, IC2.3 (VIN), IC2.4 (EN), IC3.7 (+VS), IC3.8 (~PD), R13.2, R25.1, R47.1, R53.1, S1_Gate_Driver1.2 (VIN), S1_Gate_Driver1.4 (VCC), S2#2.6 (NC), U1.2 (VIN), U1.4 (VCC), U1.18 (HI_EN), U2.5 (VCC), U3.5 (VCC), U6.5 (VCC), U9.2 (VIN), U9.4 (VCC), U10.2, U10.5 (VCC), U11.5 (VCC), U13.5 (VCC), VCO1.16 (VCC)
-5V: -5V.1, C39.2, C49.2, IC2.1 (VOUT), IC3.4 (-VS)
COMPIN: C13.1, COMPIN.1, U2.1 (OUT), VCO1.3 (COMPIN)
CTRL: CTRL.1, R20.1, R22.1, VCO1.9 (VCOIN)
EN_driver: C10.1, C20.1, C44.1, EN_DRIVER.1, R34.2, R35.2, R36.2, S1_Gate_Driver1.18 (HI_EN), U9.18 (HI_EN)
FB: C9.1, FB.1, R10.2, U2.3 (IN+)
G1: G1.1, Q1.1 (G), R41.2
G2: G2.1, Q3.1 (G), R1.2
G3: G3.1, Q2.1 (G), R42.2
G4: G4.1, Q4.1 (G), R40.2
GND: C5.2, C6.1, C7.2, C8.1, C9.2, C10.2, C12.1, C13.2, C15.1, C16.1, C17.1, C18.1, C19.2, C20.2, C22.2, C24.2, C25.1, C26.1, C27.2, C28.1, C29.1, C30.1, C33.2, C36.1, C38.1, C39.1, C41.2, C42.1, C43.1, C44.2, C48.1, C49.1, C52.1, C53.1, C54.1, C57.1, C60.1, C61.1, C62.1, GND.1, GND#2.1, GND#3.1, GND#4.1, GND#5.1, GND#6.1, GND#7.1 (L), GND#7.2 (N), GND#8.1, GND#9.1, GND#10.1, GND#11.1, GND#12.1, GND#13.1 (L), GND#13.2 (N), GND#14.1, GND#15.1, GND#16.1, GND#17.1, IC2.2 (GND), IC3.9 (EP), Q2.3 (S1), Q2.4 (S2), Q4.3 (S1), Q4.4 (S2), R7.2, R9.2, R12.1, R18.1, R19.1, R24.2, R27.2, R28.2, R29.2, R30.2, R33.1, R34.1, R35.1, R43.2, R44.2, R46.1, R51.2, R54.2, S1_Gate_Driver1.3 (VSS), S1_Gate_Driver1.7 (VSS), S1_Gate_Driver1.20 (LS_DAP), S2#2.MH1, S2#2.MH2, U1.3 (VSS), U1.7 (VSS), U1.9 (HS), U1.13 (HS), U1.14 (HS), U1.16 (HS), U1.20 (LS_DAP), U1.21 (HS_DAP), U2.2 (VEE), U3.2 (VEE), U6.3 (GND), U9.3 (VSS), U9.7 (VSS), U9.20 (LS_DAP), U10.3 (GND), U11.2, U11.3 (GND), U13.2 (VEE), VCO1.5 (INH), VCO1.8 (GND)
Is: C11.1, IC3.6 (OUT), Is.1
Is-: C3.1, C47.2, J1.2 (Ext)
Is_FB: C4.1, IC3.1 (FB), R45.2
Is_square: C22.1, Is_square.1, U3.1 (OUT), VCO1.14 (SIGIN)
unnamed: C1.1, C58.2
unnamed: C2.2, R2.1
unnamed: C3.2, R5.1
unnamed: C15.2, R20.2
unnamed: C41.1, R21.2, R31.2, U6.2
unnamed: D1.2 (A), S1_Gate_Driver1.17 (BST)
unnamed: C21.1, D1.1 (K), S1_Gate_Driver1.12 (HB)
unnamed: D2.2 (A), U9.17 (BST)
unnamed: C23.1, D2.1 (K), U9.12 (HB)
unnamed: D6.2 (A), R21.1
unnamed: D6.1 (K), R31.1, U13.1 (OUT)
unnamed: C40.1, IC2.5 (C1+)
unnamed: C40.2, IC2.6 (C1-)
unnamed: C5.1, IC3.3 (+IN), R37.2, R44.1, R46.2, TP10.1
unnamed: C4.2, IC3.2 (-IN), R4.2, R43.1, R45.1
unnamed: R2.2, R3.1
unnamed: R3.2, R4.1
unnamed: R5.2, R6.1
unnamed: R6.2, R37.1
unnamed: R28.1, S1_Gate_Driver1.5 (DHL)
unnamed: R27.1, S1_Gate_Driver1.6 (DLH)
unnamed: R41.1, S1_Gate_Driver1.10 (HO)
unnamed: R42.1, S1_Gate_Driver1.8 (LO)
unnamed: S1_Gate_Driver1.19 (PWM_LI), U11.4
unnamed: R36.1, S2#2.5 (COM)
unnamed: S2#2.4 (NO), U6.4
unnamed: R7.1, U1.5 (DHL)
unnamed: R9.1, U1.6 (DLH)
unnamed: C7.1, U1.12 (HB)
unnamed: R10.1, U1.8 (LO)
unnamed: U1.19 (PWM_LI), U9.19 (PWM_LI), U10.4
unnamed: C11.2, R12.2, R13.1, TP6.1, U3.3 (IN+)
unnamed: R29.1, U9.5 (DHL)
unnamed: R30.1, U9.6 (DLH)
unnamed: R1.1, U9.10 (HO)
unnamed: R40.1, U9.8 (LO)
unnamed: C14.2, VCO1.6 (C1A)
unnamed: C14.1, VCO1.7 (C1B)
unnamed: R22.2, VCO1.13 (PC2OUT)
unnamed: R18.2, VCO1.11 (R1)
unnamed: R19.2, VCO1.12 (R2)
Out+: C19.1, C27.1, C28.2, C29.2, C30.2, C54.2, OUT+.1 (L), OUT+.2 (N), Q1.2 (D), Q3.2 (D), R32.2
S1: C1.2, C21.2, Q1.3 (S1), Q1.4 (S2), Q2.2 (D), S1.1, S1_Gate_Driver1.9 (HS), S1_Gate_Driver1.13 (HS), S1_Gate_Driver1.14 (HS), S1_Gate_Driver1.16 (HS), S1_Gate_Driver1.21 (HS_DAP)
S2: C2.1, C23.2, C47.1, Q3.3 (S1), Q3.4 (S2), Q4.2 (D), S2.1, U9.9 (HS), U9.13 (HS), U9.14 (HS), U9.16 (HS), U9.21 (HS_DAP)
Vout_s: C24.1, R32.1, R33.2, U13.3 (IN+)
pwm: C33.1, PWM.1, U10.1, U11.1, VCO1.4 (VCOOUT)
